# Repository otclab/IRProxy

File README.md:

# IRProxy

### Descripción del Proyecto

El proyecto surge de la necesidad de enviar señales de mando infrarrojas al decodificador  de cable, de manera de controlar su operación en forma remota desde donde no es posible  utilizar su propio control remoto infrarrojo.

La solución desarrollada es utilizar el conjunto _ESP8266_ y un microcontrolador <sup>(*1)</sup> de  manera obtener la capacidad de enviar los mandos desde una red inalámbrica (y por ende _LAN_ e  Internet inclusive), los cuales serían recibidos por el módulo _ESP8266_ y enviados por  medio del su puerto _SPI_ al microcontrolador, el cual se encargaría de generar la señal  infrarroja.

El microcontrolador se incluye porque en general el módulo _ESP8266_, no tiene la capacidad para generar un patrón infrarrojo arbitrario <sup>(*2)</sup> y porque la confiabilidad del microcontrolador es muy superior a la del módulo _ESP8266_ en cualquiera de los tres lenguajes que  se  usaron (_LUA_, _Arduino_/_++C_, y _(Micro)Python_), encargándose de cebar el sistema en caso  se pierda la comunicación por cualquier motivo.  

El protocolo de comunicación elegido es el **_MQTT_**, en razón que su soporte es mas estable y simple (contrario del _COAP_ o _HTTP_) en _NodeMCU_ <sup>(*3)</sup>. 

Por otro lado como frente _GUI_  en la _PC_ se  utiliza _Python_ con soporte de la librería _Kivy_, con la cual también se tiene mejor control  sobre el tamaño de la ventana de la aplicación y es menos exigente en cuanto recursos con  respecto a un navegador, con el agregado que facilita la compilación tanto para _Windows_ como  para _Android_ de manera de obtener aplicaciones para ambos SO.

La desventaja al utilizar el protocolo _MQTT_, es que debe utilizarse un servidor intermediario  (_Broker_), al contrario que en _Android_, por el lado de la _PC_ es un problema menor, para la  cual es fácil montar un servidor, sin embargo dado que el servidor _MQTT_ puede montarse en el  servidor _NAS_ como un servicio auxiliar que puede aprovecharse para otras aplicaciones _IoT_.

Con el fin de no restringir el proyecto a su objetivo inicial y también poder usarlo aún  es sus primeras etapas de desarrollo (con solo la captura de los patrones correspondientes a  las teclas mas frecuentes) sin realizar mayores cambios al adicionar nuevos patrones para  el mismo decodificador u otros equipos, se propone implementar el código del generador en  forma genérica, de manera que la estructura de tiempos del patrón es recibida cada vez  que deba emitirse.

 El libreto de _IPython_ _"Decodificacion de las Señales Infrarrojas del Control Remoto del  "Decodificador de Movistar.ipynb"_ se encarga de procesar la captura de las señales  infrarrojas realizadas con el osciloscopio _Rigol 1052E_, verifica la rectitud de la captura  y genera los archivos _XML_ de especificación de los patrones correspondientes, los  cuales pueden ser usados por la aplicación en _Python_ para la _PC_.

### Etapa Final 
 El diseño del equipo final incluye una fuente _DC/DC_ para compartir la alimentación del  decodificador, la cual proviene de un adaptador de _12VDC_, por lo que se incluye un  convertidor _DC/DC híbrido_ el cual consta de pre-regulador reductor conmutado, operando en lazo abierto seguido de un regulador lineal de 3.3V.  El microcontrolador auxiliar también se genera la señal de excitación del pre-regulador.
 
##### Notas
 
 >- <sup>(\*1)</sup>  Para la pruebas de concepto se utilizo el PIC16F1619, un sub-siguiente periodo de prueba se realizo con el PIC16F18313. En la etapa final para trabajo constante se utiliza también el PIC16F18313.
 >- <sup>(\*2)</sup>  La versión actual del SDK del ESP8266 tiene soporte para generación de señales infrarrojas aunque para un conjunto de formatos restringido, al momento no incluye el de Samsung.
 >- <sup>(\*3)</sup>  El módulo NodeMCU fue utilizado para las pruebas iniciales, programado en Lua resulto bastante inestable, en su lugar se utilizo para el periodo de prueba la versión de Arduino para el ESP8266, el cual fue bastante estable y requirió su reinicio pocas veces. Sin embargo después de la actualización del servidor NAS (a FreeNAS 11.0) perdió la capacidad de conectarse, por lo que se decidió utilizar Micropython como lenguaje de operación para el módulo.

### Patrón de Señales
  
Para conservar la capacidad de generar un patrón cualquiera su especificación se trasmite cada vez que deba generarse, ellas incluyen la frecuencia de la portadora, su ciclo de trabajo, seguido de la secuencia de tiempos de generación y pausa de los que consta.

El formato depende del medio donde se ejecuta el interprete _PC_, _ESP8266_ o _Microcontrolador_, para la aplicación de escritorio _IRProxy_PC.py_ se utiliza el formato _XML_, la especificación es embebida en la etiqueta **_IR_CODE_**, la cual contiene las etiquetas **_SOURCE_**, **_ID_**, **_CARRIER_**, y **_PATTERN_**.

La etiquetas **_SOURCE_** e **_ID_** sirven para identificar el equipo cuyas señales de control remoto infrarrojas y la tecla o función que emulan respectivamente.

<La etiqueta **_CARRIER_** incluye dos sub-etiquetas **_PERIOD_** y **_DUTY_CYCLE_**, en las que se definen los valores del periodo y ciclo de trabajo de la portadora, la unidad utilizada para estos se define por el atributo **_unit_** definido en la etiqueta **_CARRIER_**. Por conveniencia define la resolución del generador / temporizador utilizado para generarla (

 para el PIC16F18313).

Dentro la etiqueta **_PATTERN_** se define la secuencia (_type="array"_) de pulsos, mediante la sub-etiquetas **_PULSE_**, las cuales a su vez constan de las etiquetas **_HIGH_** y **_LOW_**, que define los intervalos de activación y pausa de la portadora. Las unidades utilizadas se definen en el  atributo **_unit_**, como opción su valor puede ser _"CARRIER_PERIOD"_ implicando que las unidades  utilizadas para definir estos intervalos es el periodo de la portadora.

El formato para el envío del patrón hacia el módulo _ESP8266_, es una cadena de caracteres formada por la representación hexadecimal, de la secuencia de bytes que representan en forma consecutiva la _versión_, _número de pulsos_ el _periodo de la portadora_, su _ciclo de trabajo_, seguidos de los periodos de _activación_ y _pausa_ de cada pulso del patrón. 
En este caso no se trasmite la identificación del equipo y función a la que pertenece el patrón, pero se incluye la _versión del protocolo_, al momento solo existe la versión _1_ que es la descrita. Los valores de _127_  y _126_ se reservan para comunicación particular entre el módulo _ESP8266_ y el _microcontrolador_.

La secuencia de bytes de cada valor es la correspondiente a la codificación _VLQ_ (_Variable Length Quantity_), que utiliza el valor del bit de mayor peso de cada byte para indicar si es el último, es decir si la representación en base $128$ del valor es $A_n ...  A_1 A_0$, la secuencia utilizada es <span lang="latex">(A_0+128), (A_1+128), ... (A_n + 0)</span>. 

Nótese que los valores de los tiempos deben estar especificados en la unidad de tiempo utilizada por el microcontrolador.

Finalmente, el formato de envío al microcontrolador es la secuencia de bytes antes descrita ( no su representación hexadecimal).  Los valores reservados para la versión son utilizados para :
>- _0xFF_ : Informar que la comunicación es correcta (_keepalive_).
>- _0xFE_ : Solicitud de cebado del sistema (_reset_).

####  Limitaciones del Patrón de Señales
Desde el punto de vista de la arquitectura de la especificación y su serialización, no existe limitación, sin embargo la implementación de la generación en el _microcontrolador_ impone algunas :
  >- El campo del número de pulsos esta limitado a 255. En la practica el número de pulsos esta limitado por el almacenamiento reservado al patrón, en la versión actual 46 bytes.
  >- Los periodos de tiempo se limitan a 65535 de las unidades respectivas.

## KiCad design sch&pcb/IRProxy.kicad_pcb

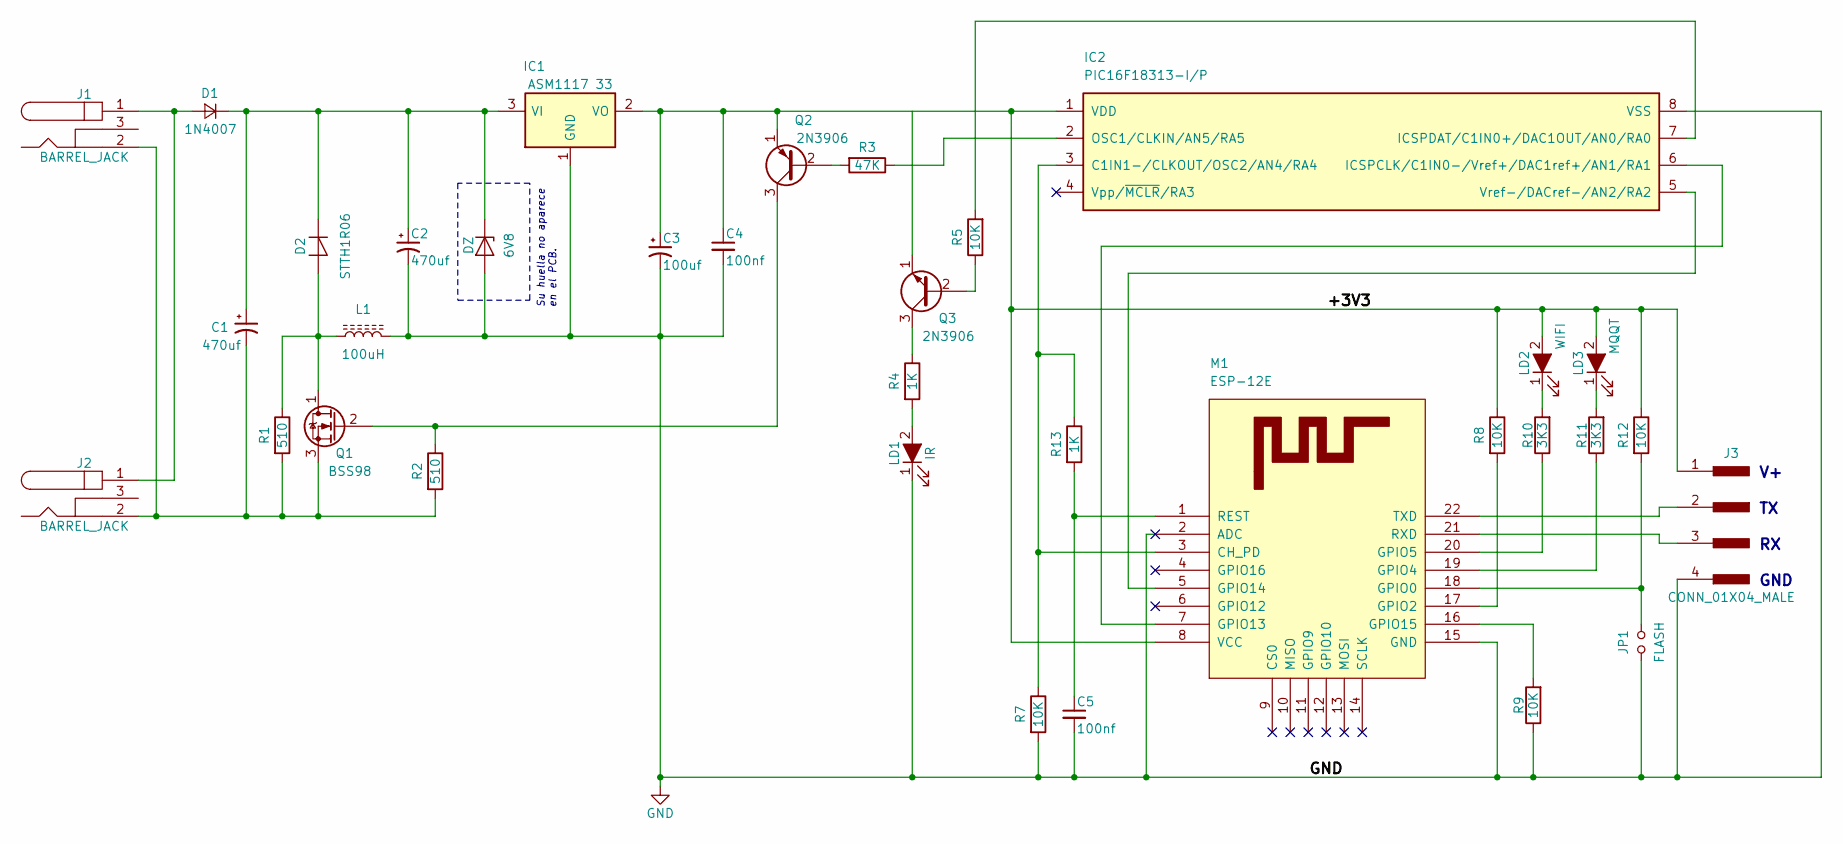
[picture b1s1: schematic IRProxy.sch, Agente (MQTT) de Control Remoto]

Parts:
C1, C2: 470uf; CP_Radial_D6.3mm_P2.50mm
C3: 100uf; CP_Radial_D5.0mm_P2.50mm
C4, C5: 100nf; C_Disc_D3.0mm_W2.0mm_P2.50mm
D1: 1N4007; D_DO-15_P10.16mm_Horizontal
D2: STTH1R06; D_DO-15_P10.16mm_Horizontal
DZ: 6V8
IC1: ASM1117 33; SOT-223
IC2: PIC16F18313-I/P; DIP-8_W7.62mm
J1, J2: BARREL_JACK
J3: CONN_01X04_MALE; Pin_Header_Angled_1x04_Pitch2.54mm
JP1: FLASH; WireConnection_0.80mmDrill
L1: 100uH; L_Toroid_Horizontal_D16.8mm_P14.70mm_Vishay_TJ3
LD1: IR; LED_D5.0mm_Horizontal_O3.81mm_Z15.0mm
LD2: WIFI; LED-3MM
LD3: MQQT; LED-3MM
M1: ESP-12E; ESP-12E_SMD
Q1: BSS98; TO-92_Molded_Wide
Q2, Q3: 2N3906; TO-92_Molded_Wide
R1, R2: 510; R_Axial_DIN0207_L6.3mm_D2.5mm_P10.16mm_Horizontal
R3: 47K; R_Axial_DIN0207_L6.3mm_D2.5mm_P10.16mm_Horizontal
R4, R13: 1K; R_Axial_DIN0207_L6.3mm_D2.5mm_P10.16mm_Horizontal
R5, R7, R8, R9, R12: 10K; R_Axial_DIN0207_L6.3mm_D2.5mm_P10.16mm_Horizontal
R10, R11: 3K3; R_Axial_DIN0207_L6.3mm_D2.5mm_P10.16mm_Horizontal

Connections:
/+3V3: C3.1, C4.1, IC1.2 (VO), IC2.1 (VDD), J3.1, LD2.2 (A), LD3.2 (A), M1.8 (VCC), Q2.1 (E), R8.1, R12.1
GND: C2.2, C3.2, C4.2, C5.2, DZ.2 (A), IC1.1 (GND), IC2.8 (VSS), J3.4, JP1.2, L1.2, LD1.1 (K), M1.2 (ADC), M1.15 (GND), R7.2, R9.1
unnamed: C1.1, C2.1, D1.1 (K), D2.1 (K), DZ.1 (K), IC1.3 (VI)
unnamed: C1.2, J1.2, J2.2, Q1.3 (S), R1.2, R2.2
unnamed: C5.1, M1.1 (REST), R13.2
unnamed: D1.2 (A), J1.1, J2.1
unnamed: D2.2 (A), L1.1, Q1.1 (D), R1.1
unnamed: IC2.2 (OSC1/CLKIN/AN5/RA5), R3.1
unnamed: IC2.3 (C1IN1-/CLKOUT/OSC2/AN4/RA4), M1.3 (CH_PD), R7.1, R13.1
unnamed: IC2.5 (Vref-/DACref-/AN2/RA2), M1.5 (GPIO14)
unnamed: IC2.6 (ICSPCLK/C1IN0-/Vref+/DAC1ref+/AN1/RA1), M1.7 (GPIO13)
unnamed: IC2.7 (ICSPDAT/C1IN0+/DAC1OUT/AN0/RA0), R5.2
unnamed: J3.2, M1.22 (TXD)
unnamed: J3.3, M1.21 (RXD)
unnamed: JP1.1, M1.18 (GPIO0), R12.2
unnamed: LD1.2 (A), R4.2
unnamed: LD2.1 (K), R10.2
unnamed: LD3.1 (K), R11.2
unnamed: M1.16 (GPIO15), R9.2
unnamed: M1.17 (GPIO2), R8.2
unnamed: M1.19 (GPIO4), R11.1
unnamed: M1.20 (GPIO5), R10.1
unnamed: Q1.2 (G), Q2.3 (C), R2.1
unnamed: Q2.2 (B), R3.2
unnamed: Q3.2 (B), R5.1
unnamed: Q3.3 (C), R4.1

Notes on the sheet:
GND
Su huella no aparece en el PCB.

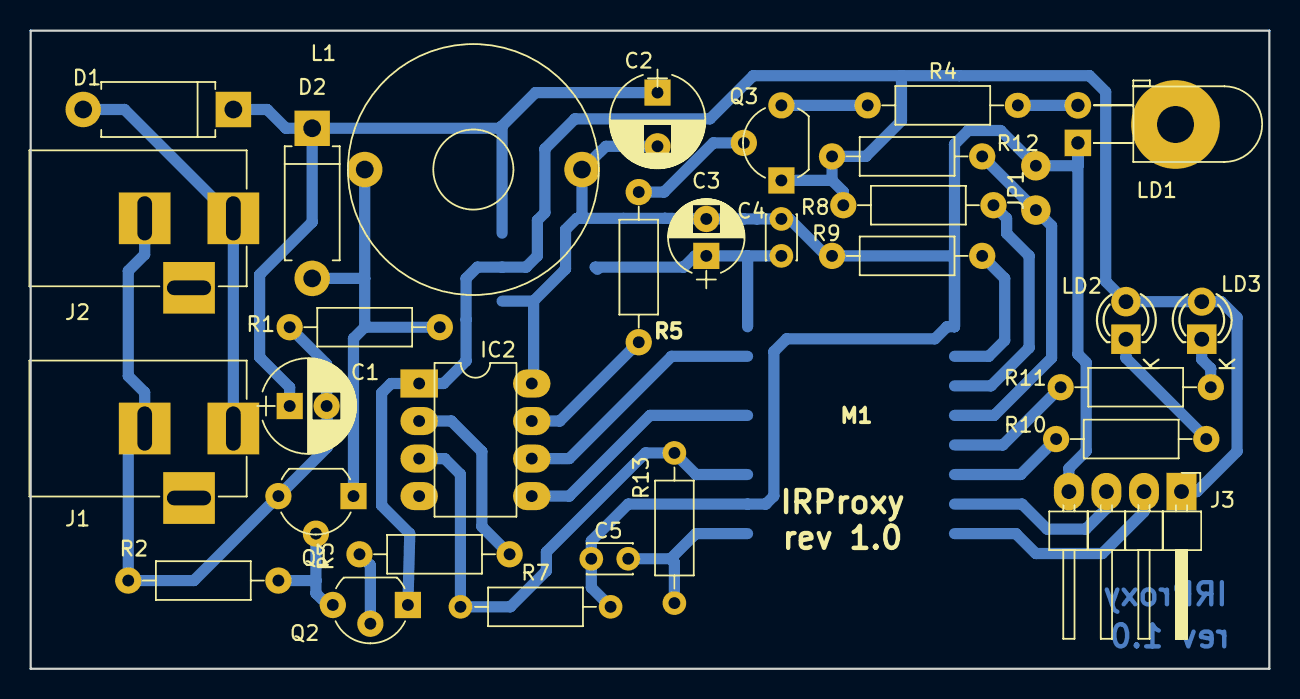
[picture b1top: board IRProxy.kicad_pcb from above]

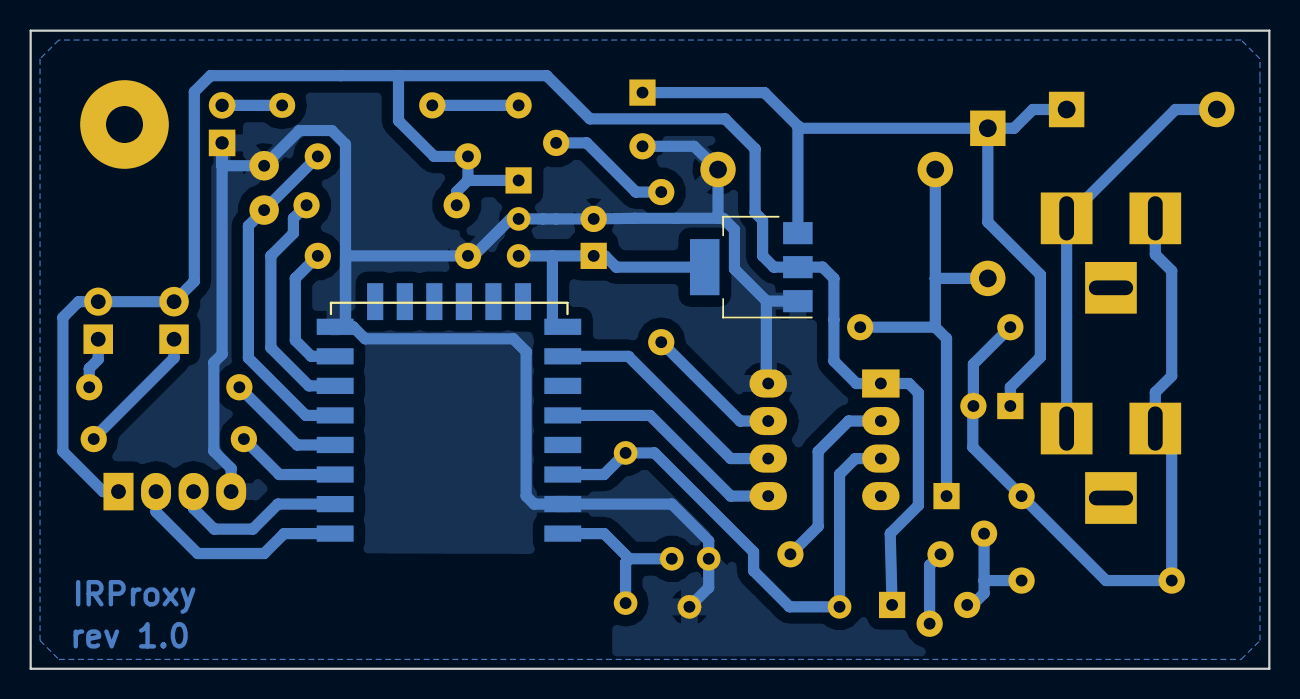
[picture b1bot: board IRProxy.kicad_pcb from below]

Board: 2 copper layers, 83.8 x 43.2 mm, 33 parts (2 on the bottom side), 26 nets.

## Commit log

2019-03-07 IRProxy basada en MycroPython
    Importación inicial del repetidor de señales de control remoto infrarrojo : IRProxy
2019-03-07 Edit README.md y .gitignore
2019-03-10 Refina la secuencia de encendido del módulo ESP8266
    Se incluye un retardo entre el encendido del módulo y el de la fuente DC/DC del pre-regulador.
2019-03-10 Corrige la presentación de las redes disponibles.
2019-03-10 Se modifica el nombre simbólico del Broker.
2019-03-10 Se actualiza el nombre del modulo de la aplicación en main.py
2019-03-10 Actualizando la portada, README.md
2019-03-12 Se repara la falta de parpadeo del LED de conexión al broker al recibir un mensaje.
2020-04-14 Fija la posición por defecto.
    Se define la posición de arranque, para ubicarse justo sobre la ventana PIP.
2020-04-14 Reajuste de la tensión de entrada del pre-regulador.
    Se prepara el pre-regulador para una entrada de 12V,.
2020-05-26 Flow para Node-Red
    Se añade el flujo para Node-Red, que implementa un interfaz UI para navegadores., particularmente desde celulares inteligentes.
2020-06-01 Se añade la documentación condensada (doc).
    Se añade el subdirectorio doc con la documentación condensada del circuito esquemático e impreso .
2020-06-01 Se unifica la dependencia en IRProxy.lib
    Se adapta el esquemático para eliminar los archivos *rescue y *cache, en este punto las partes incluidas en el solo dependen de IRProxy.lib
